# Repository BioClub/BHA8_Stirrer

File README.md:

## BHA Stirrer
This repo contains the designs and source files of a **DIY Magnetic Stirrer**. Such a device is used to stir liquids continiously for a long period of time. The optional heating pad keeps the liquid warm, it is not design for boiling or cooking.

- This repo is a clone from https://gitlab.waag.org/biohack/BHA_Stirrer, please go there for the history and provenience. 
- `BoM` will be specific to Japan.
- We will also described more `hacky` ways (old computer fans, etc) to build the Stirrer.

## Navigation the repo

 	BHA_Stirrer/				main repo
 	|-- Magnetic-Stirrer-kicad/		wiring documentation
 	BoM.md					Bill of Materials
 	Magnetic-Stirrer-Cut-Sheet-3mm.svg	Laser cut sheet 3mm
 	Magnetic-Stirrer-Cut-Sheet-4mm.svg	Laser cut sheet 4mm
 	Magnetic-Stirrer.f3d			Fusion 360 model

## Releases

The magnetic stirrer v4.0 release contains the following:

* 2023 BHA8 Design

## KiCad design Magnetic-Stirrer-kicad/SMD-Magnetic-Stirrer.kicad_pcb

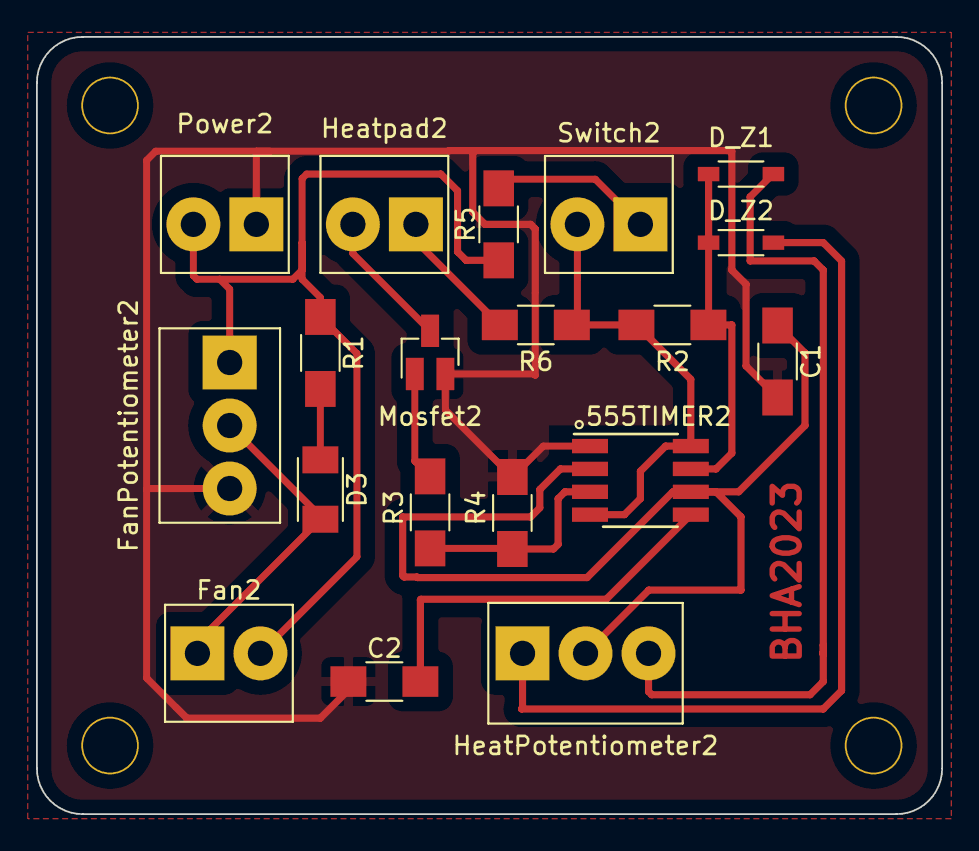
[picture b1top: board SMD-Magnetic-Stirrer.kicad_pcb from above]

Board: 2 copper layers, 50.3 x 43.2 mm, 19 parts (0 on the bottom side), 15 nets.

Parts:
555TIMER2: NE555P; SOIC-8_3.9x4.9mm_P1.27mm
C1: 2.2uF; C_1206
C2: 100nF; C_1206
D3: D_Schottky_100V_1A; SOD-123T
D_Z1, D_Z2: D_Zener; SOD-123
Fan2: Screw_Terminal_01x02_P3.5mm; TerminalBlock_OnShore_1x02_P3.50mm_Horizontal
FanPotentiometer2: Screw_Terminal_01x03_P3.5mm; TerminalBlock_OnShore_1x03_P3.50mm_Horizontal
HeatPotentiometer2: Screw_Terminal_01x03_P3.5mm; TerminalBlock_OnShore_1x03_P3.50mm_Horizontal
Heatpad2: Screw_Terminal_01x02_P3.5mm; TerminalBlock_OnShore_1x02_P3.50mm_Horizontal
Mosfet2: MOSFET_N-CH_30V_1.7A; SOT-23
Power2: Screw_Terminal_01x02_P3.5mm; TerminalBlock_OnShore_1x02_P3.50mm_Horizontal
R1: 470; R_1206
R2, R3: 1k; R_1206
R4: 100k; R_1206
R5, R6: 0; R_1206
Switch2: Screw_Terminal_01x02_P3.5mm; TerminalBlock_OnShore_1x02_P3.50mm_Horizontal

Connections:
unnamed: 555TIMER2.3 (Q), R3.2, R4.1
unnamed: 555TIMER2.5 (CV), C2.2
unnamed: 555TIMER2.4 (R), 555TIMER2.8 (VCC), R2.2, R6.1, Switch2.2
unnamed: 555TIMER2.2 (TR), 555TIMER2.6 (THR), C1.1, HeatPotentiometer2.2
unnamed: D3.2 (A), R1.2
unnamed: D_Z2.1 (K), HeatPotentiometer2.1
unnamed: 555TIMER2.7 (DIS), D_Z1.1 (K), D_Z2.2 (A), R2.1
unnamed: D3.1 (K), Fan2.1, FanPotentiometer2.2
unnamed: D_Z1.2 (A), HeatPotentiometer2.3
unnamed: Heatpad2.1, R6.2
unnamed: Heatpad2.2, Mosfet2.3 (D)
unnamed: Fan2.2, FanPotentiometer2.1, Power2.2, R1.1, R5.1
unnamed: Mosfet2.1 (G), R3.1
unnamed: R5.2, Switch2.1
PWR_GND: 555TIMER2.1 (GND), C1.2, C2.1, FanPotentiometer2.3, Mosfet2.2 (S), Power2.1, R4.2

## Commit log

2023-04-03 Clone from Waag's GitLab
    Clone from Waag's GitLab https://gitlab.waag.org/biohack/BHA_Stirrer
2023-04-04 KiCAD Latest
2023-04-08 Zener and Mosfet Info from Maarten
